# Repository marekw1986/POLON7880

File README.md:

# POLON 7880

## Overview

This is repository stores modified version of TinyBasic interpreter for 8080 based microcomputers. 
It has been customized to my homemade system, based on Polish clone of mentioned CPU - 
CEMI MCY7880. Original code has been supplemented with I/O routines supporting built-in 
peripherals.

Computer is described on my [Hackaday.io profile](https://hackaday.io/project/161333-polon-7880)

This project is still in development.

## Required tools

You need an [a86 cross assembler](https://github.com/glitchwrks/a85) to asemble this project.

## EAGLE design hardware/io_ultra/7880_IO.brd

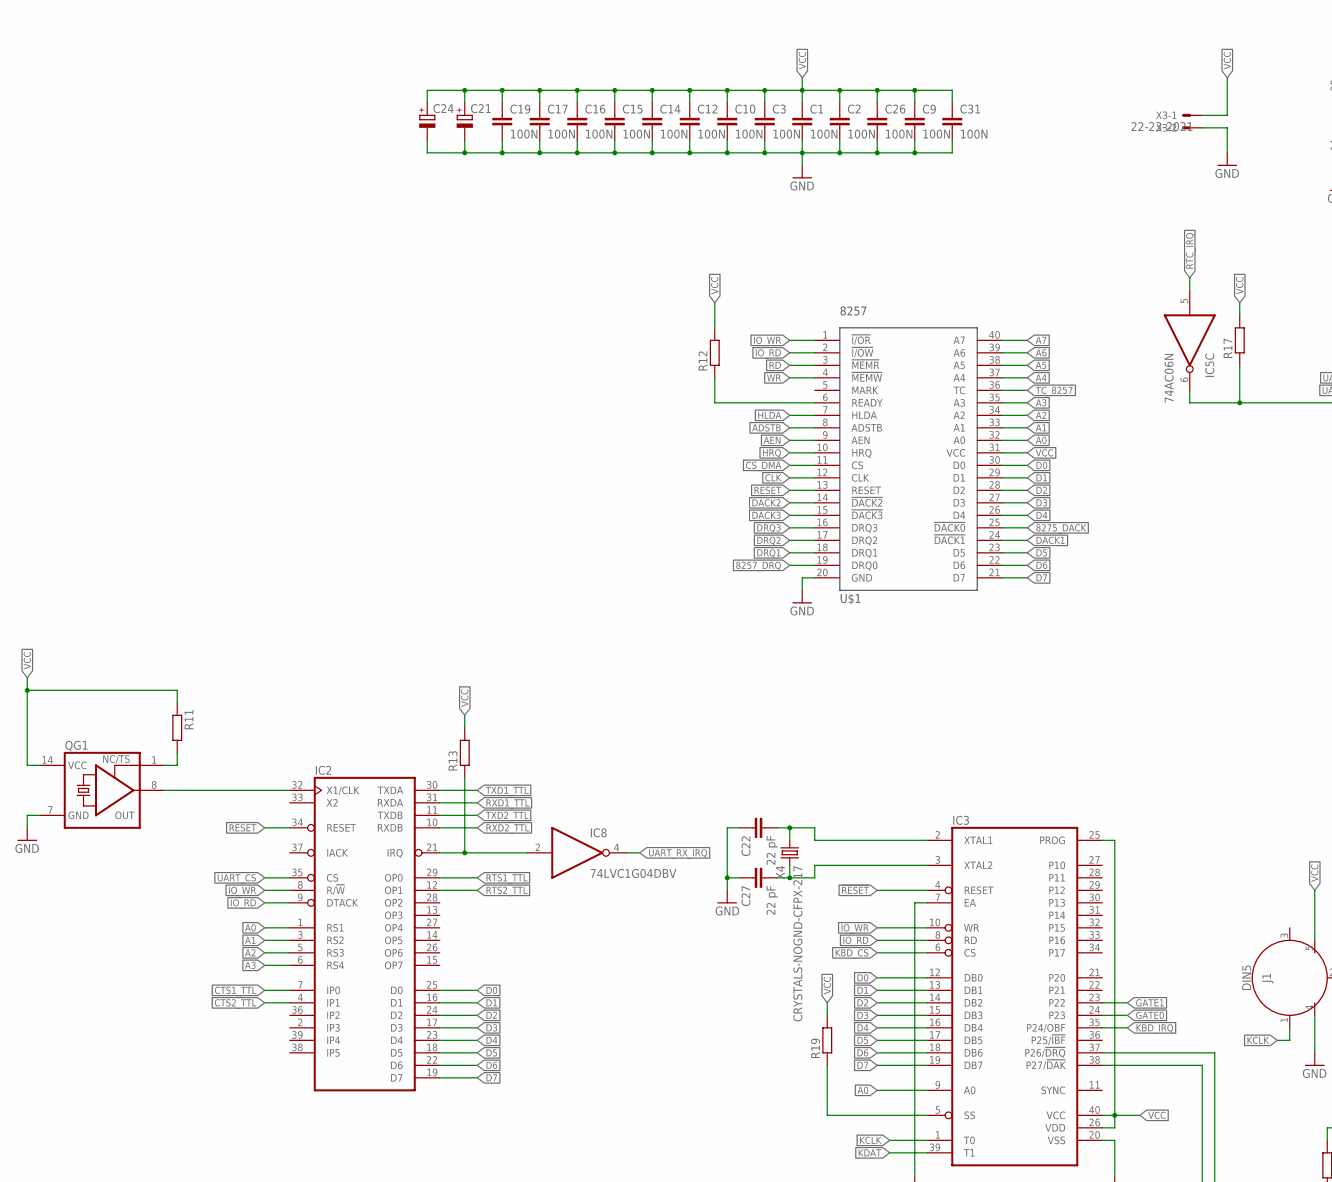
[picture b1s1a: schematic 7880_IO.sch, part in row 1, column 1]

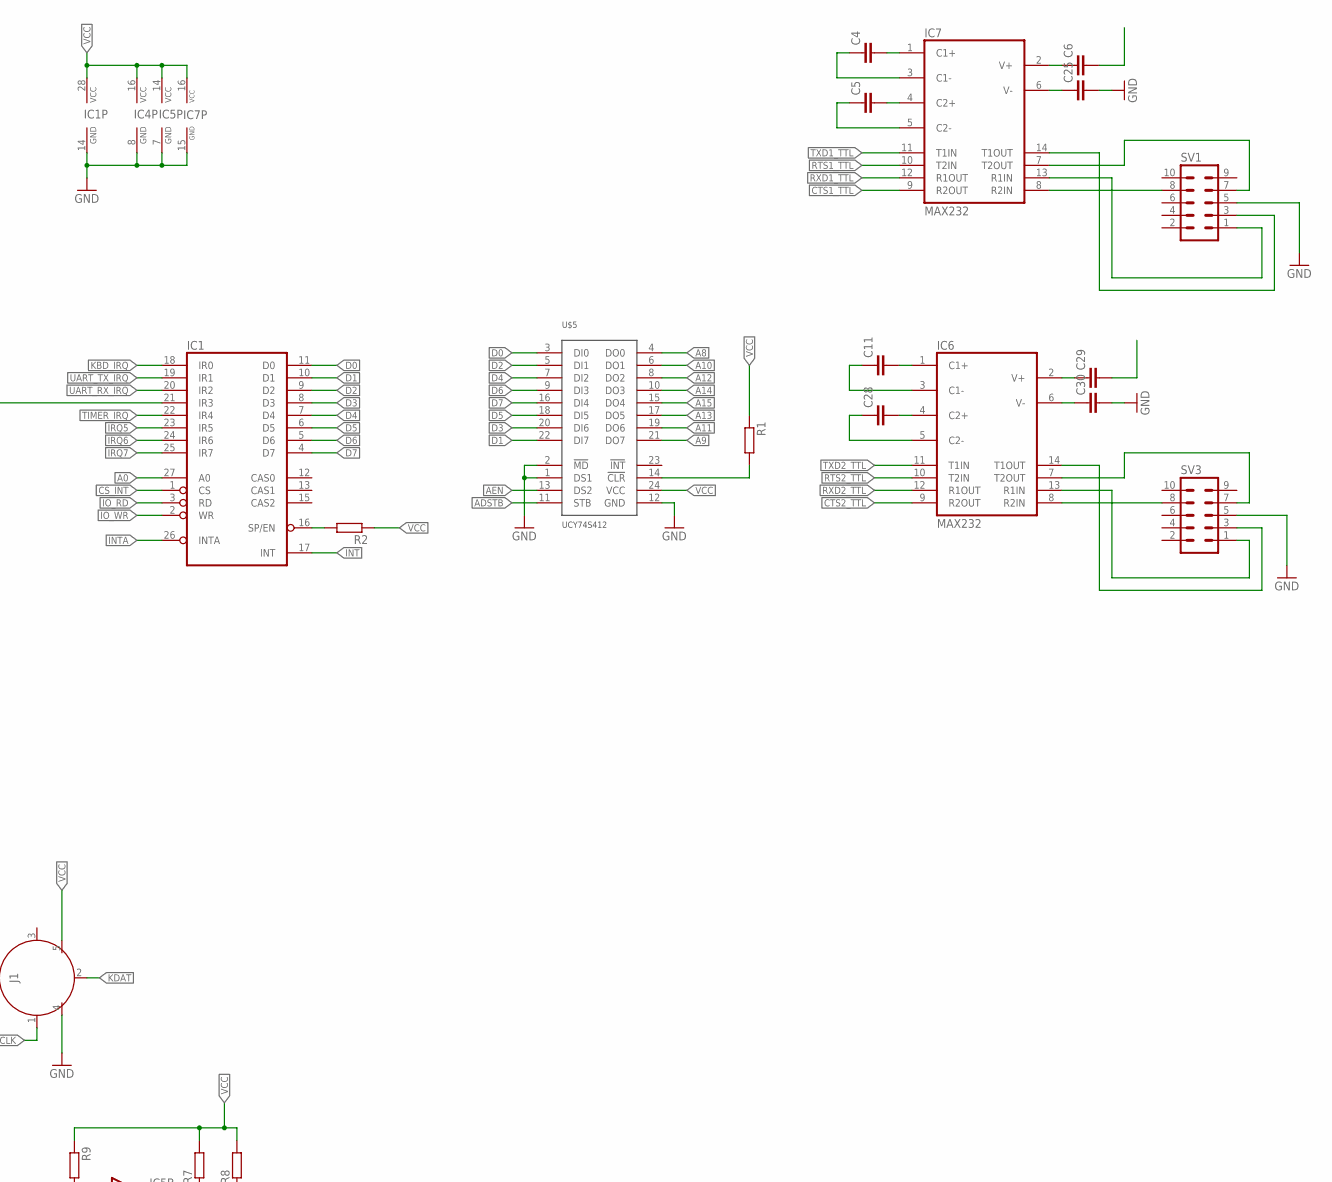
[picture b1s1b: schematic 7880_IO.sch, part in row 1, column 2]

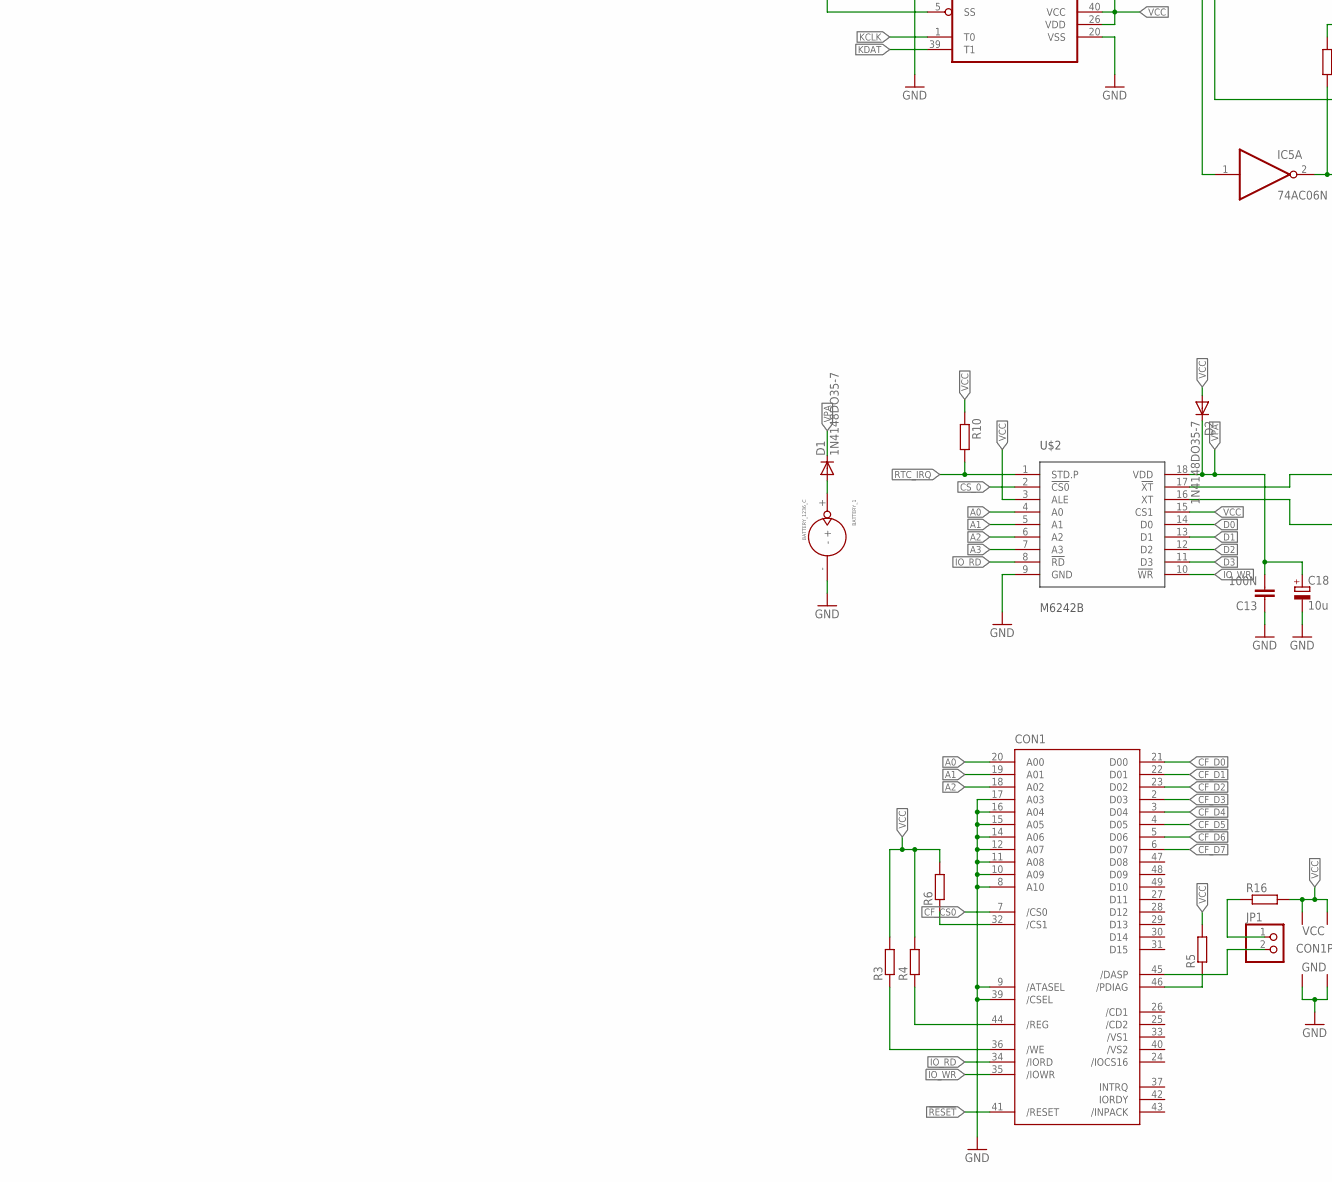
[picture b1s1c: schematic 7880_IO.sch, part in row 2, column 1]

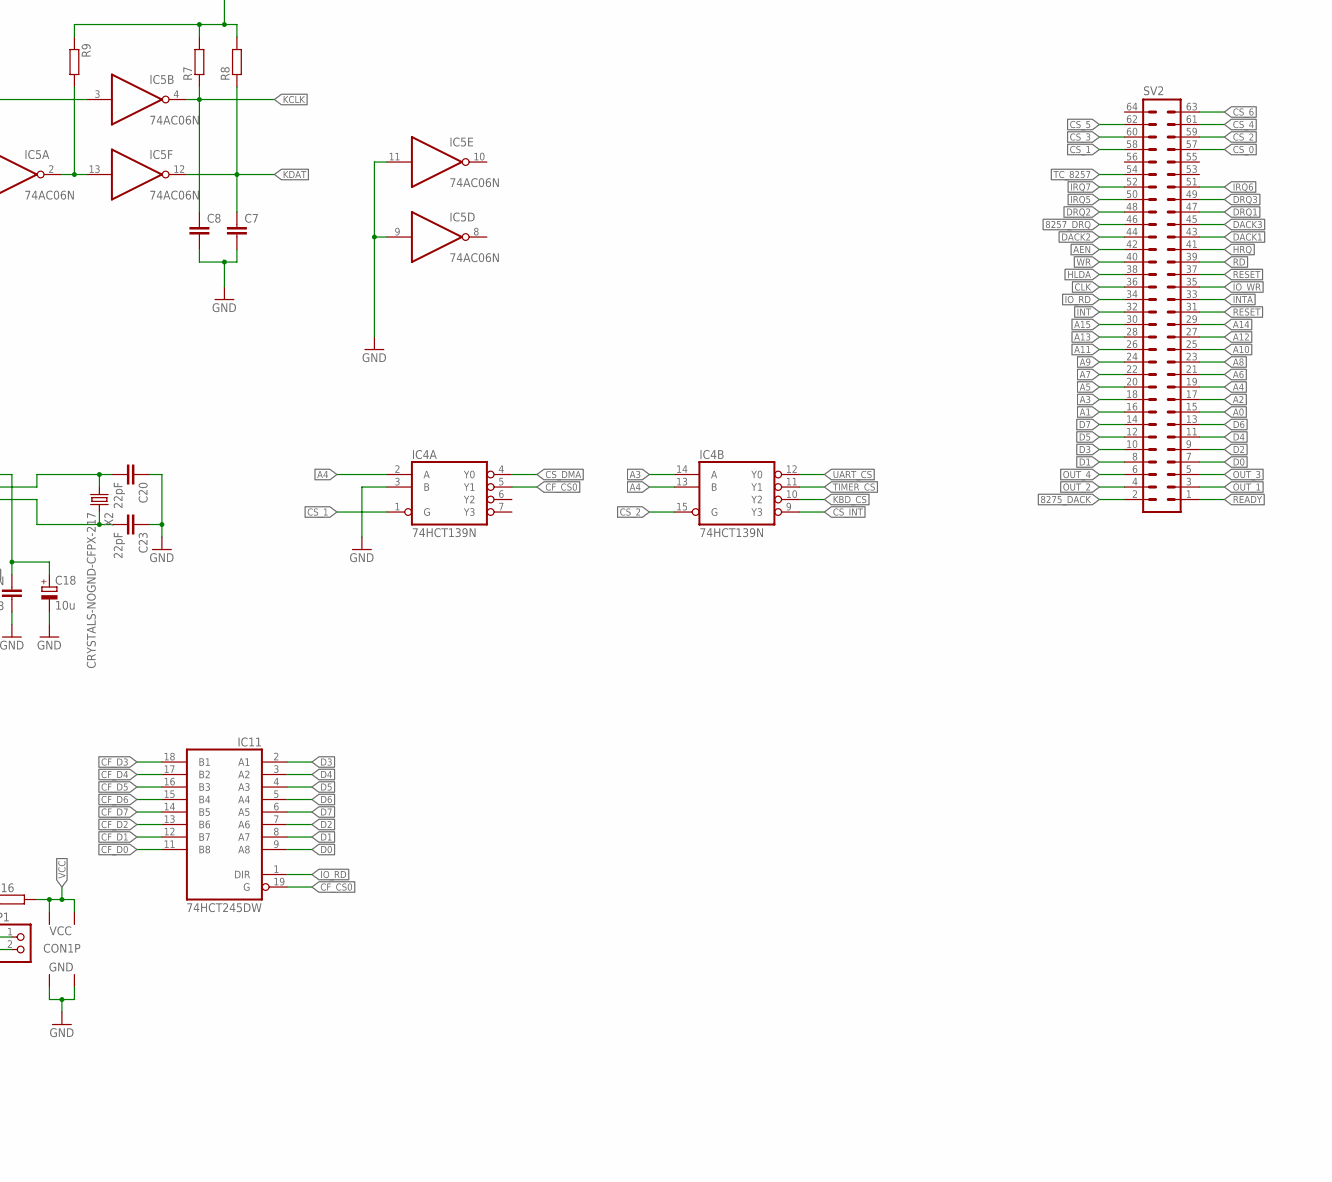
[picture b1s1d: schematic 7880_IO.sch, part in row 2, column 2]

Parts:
BATTERY_1: BATTERY_1236_C
C1, C2, C3, C9, C10, C12, C13, C14, C15, C16, C17, C19, C26, C31: 100N; C0603
C4, C5, C6, C7, C8, C11, C25, C28, C29, C30: C-EUC0603; C0603
C18: 10u; SMC_B
C20, C23: 22pF; C0603
C21: CPOL-EUE3.5-8; E3,5-8
C22, C27: 22 pF; C0603
C24: CPOL-EUSMCB; SMC_B
CON1: CF-CARD-IDE_MODE; MI20-50PD-SF
D1, D2: 1N4148DO35-7; DO35-7
IC1: 8259A; DIL28-6
IC2: MC68681P; DIL40
IC3: UPI-8042AH; DIL40
IC4: 74HCT139N; DIL16
IC5: 74AC06N; DIL14
IC6, IC7: MAX232; DIL16
IC8: 74LVC1G04DBV; SOT23-5
IC11: 74HCT245DW; SO20W
J1: DIN5; DIN5-RA-PTH
JP1: PINHD-1X2; 1X02
QG1: XO-14; DIL14S
R1, R2, R3, R6, R9, R10, R11, R12, R16: R-EU_R0603; R0603
R4, R13, R17: R-EU_0204/7; 0204/7
R5: R-EU_0207/10; 0207/10
R7, R19: R-EU_0204/5; 0204/5
R8: R-EU_M0805; M0805
SV1, SV3: ML10
SV2: ML64L
U$1: 8257; DIL40
U$2: M6242B; DIL18
U$5: UCY74S412; DIL24-6
X2, X4: CRYSTALS-NOGND-CFPX-217; 3.2X1.5-2-PAD
X3: 22-23-2021

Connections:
8257_DRQ: SV2.46, U$1.19 (DRQ0)
8275_DACK: SV2.2, U$1.25 (!DACK0)
2457600HZ: IC2.32 (X1/CLK), QG1.8 (OUT)
!RESET: CON1.41 (/RESET), IC3.4 (RESET), SV2.37
A0: CON1.20 (A00), IC1.27 (A0), IC2.1 (RS1), IC3.9 (A0), SV2.15, U$1.32 (A0), U$2.4 (A0)
A1: CON1.19 (A01), IC2.3 (RS2), SV2.16, U$1.33 (A1), U$2.5 (A1)
A2: CON1.18 (A02), IC2.5 (RS3), SV2.17, U$1.34 (A2), U$2.6 (A2)
A3: IC2.6 (RS4), IC4.14 (A), SV2.18, U$1.35 (A3), U$2.7 (A3)
A4: IC4.2 (A), IC4.13 (B), SV2.19, U$1.37 (A4)
A5: SV2.20, U$1.38 (A5)
A6: SV2.21, U$1.39 (A6)
A7: SV2.22, U$1.40 (A7)
A8: SV2.23, U$5.4 (DO0)
A9: SV2.24, U$5.21 (DO7)
A10: SV2.25, U$5.6 (DO1)
A11: SV2.26, U$5.19 (DO6)
A12: SV2.27, U$5.8 (DO2)
A13: SV2.28, U$5.17 (DO5)
A14: SV2.29, U$5.10 (DO3)
A15: SV2.30, U$5.15 (DO4)
ADSTB: U$1.8 (ADSTB), U$5.11 (STB)
AEN: SV2.42, U$1.9 (AEN), U$5.13 (DS2)
CF_CS0: CON1.7 (/CS0), IC4.5 (Y1), IC11.19 (G)
CF_D0: CON1.21 (D00), IC11.11 (B8)
CF_D1: CON1.22 (D01), IC11.12 (B7)
CF_D2: CON1.23 (D02), IC11.13 (B6)
CF_D3: CON1.2 (D03), IC11.18 (B1)
CF_D4: CON1.3 (D04), IC11.17 (B2)
CF_D5: CON1.4 (D05), IC11.16 (B3)
CF_D6: CON1.5 (D06), IC11.15 (B4)
CF_D7: CON1.6 (D07), IC11.14 (B5)
CLK: SV2.36, U$1.12 (CLK)
COM1_CTS: IC7.8 (R2IN), SV1.8
COM1_RXD: IC7.13 (R1IN), SV1.1
COM1_TXD: IC7.14 (T1OUT), SV1.3
CS_0: SV2.57, U$2.2 (!CS0)
CS_1: IC4.1 (G), SV2.58
CS_2: IC4.15 (G), SV2.59
CS_3: SV2.60
CS_4: SV2.61
CS_5: SV2.62
CS_6: SV2.63
CS_DMA: IC4.4 (Y0), U$1.11 (CS)
CS_INT: IC1.1 (CS), IC4.9 (Y3)
CTS1_TTL: IC2.7 (IP0), IC7.9 (R2OUT)
CTS2_TTL: IC2.4 (IP1), IC6.9 (R2OUT)
D0: IC1.11 (D0), IC2.25 (D0), IC3.12 (DB0), IC11.9 (A8), SV2.7, U$1.30 (D0), U$2.14 (D0), U$5.3 (DI0)
D1: IC1.10 (D1), IC2.16 (D1), IC3.13 (DB1), IC11.8 (A7), SV2.8, U$1.29 (D1), U$2.13 (D1), U$5.22 (DI7)
D2: IC1.9 (D2), IC2.24 (D2), IC3.14 (DB2), IC11.7 (A6), SV2.9, U$1.28 (D2), U$2.12 (D2), U$5.5 (DI1)
D3: IC1.8 (D3), IC2.17 (D3), IC3.15 (DB3), IC11.2 (A1), SV2.10, U$1.27 (D3), U$2.11 (D3), U$5.20 (DI6)
D4: IC1.7 (D4), IC2.23 (D4), IC3.16 (DB4), IC11.3 (A2), SV2.11, U$1.26 (D4), U$5.7 (DI2)
D5: IC1.6 (D5), IC2.18 (D5), IC3.17 (DB5), IC11.4 (A3), SV2.12, U$1.23 (D5), U$5.18 (DI5)
D6: IC1.5 (D6), IC2.22 (D6), IC3.18 (DB6), IC11.5 (A4), SV2.13, U$1.22 (D6), U$5.9 (DI3)
D7: IC1.4 (D7), IC2.19 (D7), IC3.19 (DB7), IC11.6 (A5), SV2.14, U$1.21 (D7), U$5.16 (DI4)
DACK1: SV2.43, U$1.24 (!DACK1)
DACK2: SV2.44, U$1.14 (!DACK2)
DACK3: SV2.45, U$1.15 (!DACK3)
DRQ1: SV2.47, U$1.18 (DRQ1)
DRQ2: SV2.48, U$1.17 (DRQ2)
DRQ3: SV2.49, U$1.16 (DRQ3)
GATE0: IC3.24 (P23)
GATE1: IC3.23 (P22)
GND: BATTERY_1.-, C1.2, C2.2, C3.2, C7.2, C8.2, C9.2, C10.2, C12.2, C13.1, C14.2, C15.2, C16.2, C17.2, C18.-, C19.2, C20.1, C21.-, C22.1, C23.1, C24.-, C25.2, C26.2, C27.1, C30.2, C31.2, CON1.1 (GND1), CON1.8 (A10), CON1.9 (/ATASEL), CON1.10 (A09), CON1.11 (A08), CON1.12 (A07), CON1.14 (A06), CON1.15 (A05), CON1.16 (A04), CON1.17 (A03), CON1.39 (/CSEL), CON1.50 (GND2), IC1.14 (GND), IC2.20 (GND), IC3.7 (EA), IC3.20 (VSS), IC4.3 (B), IC4.8 (GND), IC5.7 (GND), IC5.9 (I), IC5.11 (I), IC6.15 (GND), IC7.15 (GND), IC8.3 (GND), IC11.10 (GND), J1.4, QG1.7 (GND), SV1.5, SV3.5, U$1.20 (GND), U$2.9 (GND), U$5.1 (DS1), U$5.2 (!MD), U$5.12 (GND), X3.2
HLDA: SV2.38, U$1.7 (HLDA)
HRQ: SV2.41, U$1.10 (HRQ)
INT: IC1.17 (INT), SV2.32
INTA: IC1.26 (INTA), SV2.33
IO_RD: CON1.34 (/IORD), IC1.3 (RD), IC2.9 (DTACK), IC3.8 (RD), IC11.1 (DIR), SV2.34, U$1.2 (!I/OW), U$2.8 (!RD)
IO_WR: CON1.35 (/IOWR), IC1.2 (WR), IC2.8 (R/!W), IC3.10 (WR), SV2.35, U$1.1 (!I/OR), U$2.10 (!WR)
IRQ5: IC1.23 (IR5), SV2.50
IRQ6: IC1.24 (IR6), SV2.51
IRQ7: IC1.25 (IR7), SV2.52
KBD_CS: IC3.6 (CS), IC4.10 (Y2)
KBD_IRQ: IC1.18 (IR0), IC3.35 (P24/OBF)
KCLK: C8.1, IC3.1 (T0), IC5.4 (O), J1.1, R7.1
KDAT: C7.1, IC3.39 (T1), IC5.12 (O), J1.2, R8.1
unnamed: R1.2, U$5.14 (!CLR)
unnamed: IC1.16 (SP/EN), R2.2
unnamed: IC3.38 (P27/!DAK), IC5.1 (I)
unnamed: CON1.36 (/WE), R3.1
unnamed: R12.1, U$1.6 (READY)
unnamed: QG1.1 (TS), R11.2
unnamed: IC2.21 (IRQ), IC8.2 (I), R13.1
unnamed: C4.2, IC7.1 (C1+)
unnamed: C5.2, IC7.4 (C2+)
unnamed: C5.1, IC7.5 (C2-)
unnamed: C4.1, IC7.3 (C1-)
unnamed: C6.1, IC7.2 (V+)
unnamed: C25.1, IC7.6 (V-)
unnamed: IC6.7 (T2OUT), SV3.7
unnamed: C11.2, IC6.1 (C1+)
unnamed: IC3.37 (P26/!DRQ), IC5.3 (I)
unnamed: IC7.7 (T2OUT), SV1.7
unnamed: CON1.44 (/REG), R4.1
unnamed: IC5.2 (O), IC5.13 (I), R9.2
unnamed: CON1.46 (/PDIAG), R5.1
unnamed: BATTERY_1.+, D1.A
unnamed: C28.2, IC6.4 (C2+)
unnamed: C28.1, IC6.5 (C2-)
unnamed: CON1.32 (/CS1), R6.1
unnamed: C11.1, IC6.3 (C1-)
unnamed: C29.1, IC6.2 (V+)
unnamed: IC1.21 (IR3), IC5.6 (O), R17.1
unnamed: CON1.45 (/DASP), JP1.2
unnamed: JP1.1, R16.1
unnamed: IC3.5 (SS), R19.1
unnamed: IC6.13 (R1IN), SV3.1
unnamed: IC6.14 (T1OUT), SV3.3
unnamed: IC6.8 (R2IN), SV3.8
unnamed: C30.1, IC6.6 (V-)
OUT_1: SV2.3
OUT_2: SV2.4
OUT_3: SV2.5
OUT_4: SV2.6
RD: SV2.39, U$1.3 (!MEMR)
READY: SV2.1
RESET: IC2.34 (RESET), SV2.31, U$1.13 (RESET)
RTC_IRQ: IC5.5 (I), R10.2, U$2.1 (STD.P)
RTS1_TTL: IC2.29 (OP0), IC7.10 (T2IN)
RTS2_TTL: IC2.12 (OP1), IC6.10 (T2IN)
RXD1_TTL: IC2.31 (RXDA), IC7.12 (R1OUT)
RXD2_TTL: IC2.10 (RXDB), IC6.12 (R1OUT)
SOSCI: C20.2, U$2.17 (!XT), X2.1
SOSCO: C23.2, U$2.16 (XT), X2.2
TC_8257: SV2.54, U$1.36 (TC)
TIMER_CS: IC4.11 (Y1)
TIMER_IRQ: IC1.22 (IR4)
TXD1_TTL: IC2.30 (TXDA), IC7.11 (T1IN)
TXD2_TTL: IC2.11 (TXDB), IC6.11 (T1IN)
UART_CS: IC2.35 (CS), IC4.12 (Y0)
UART_RX_IRQ: IC1.20 (IR2), IC8.4 (O)
UART_TX_IRQ: IC1.19 (IR1)
VCC: C1.1, C2.1, C3.1, C6.2, C9.1, C10.1, C12.1, C14.1, C15.1, C16.1, C17.1, C19.1, C21.+, C24.+, C26.1, C29.2, C31.1, CON1.13 (VCC2), CON1.38 (VCC1), D2.A, IC1.28 (VCC), IC2.40 (VCC), IC3.25 (PROG), IC3.26 (VDD), IC3.40 (VCC), IC4.16 (VCC), IC5.14 (VCC), IC6.16 (VCC), IC7.16 (VCC), IC8.5 (VCC), IC11.20 (VCC), J1.5, QG1.14 (VCC), R1.1, R2.1, R3.2, R4.2, R5.2, R6.2, R7.2, R8.2, R9.1, R10.1, R11.1, R12.2, R13.2, R16.2, R17.2, R19.2, U$1.31 (VCC), U$2.3 (ALE), U$2.15 (CS1), U$5.24 (VCC), X3.1
VPA: C13.2, C18.+, D1.C, D2.C, U$2.18 (VDD)
WR: SV2.40, U$1.4 (!MEMW)
XTAL1: C22.2, IC3.2 (XTAL1), X4.1
XTAL2: C27.2, IC3.3 (XTAL2), X4.2

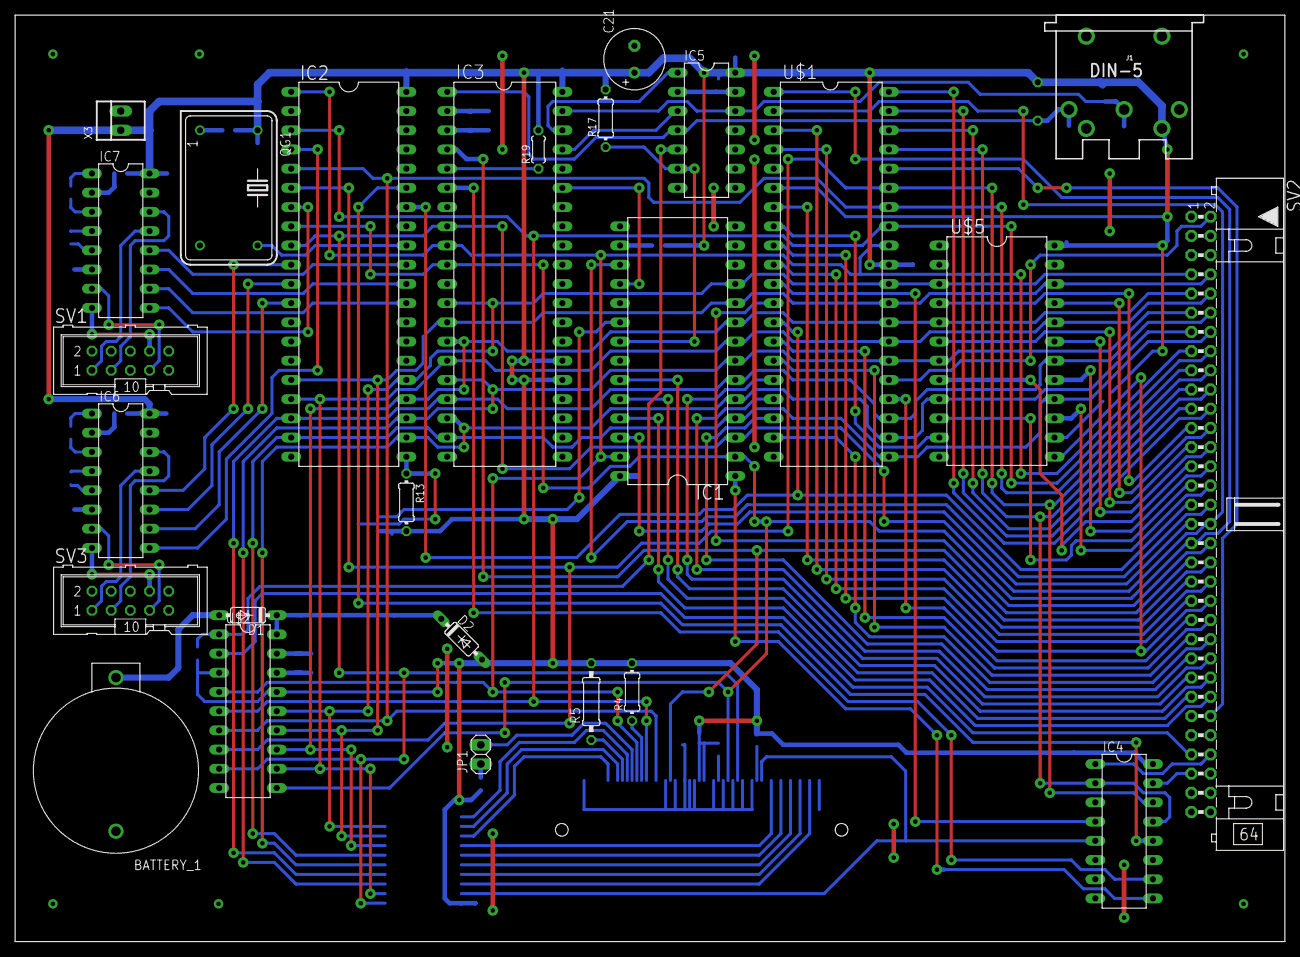
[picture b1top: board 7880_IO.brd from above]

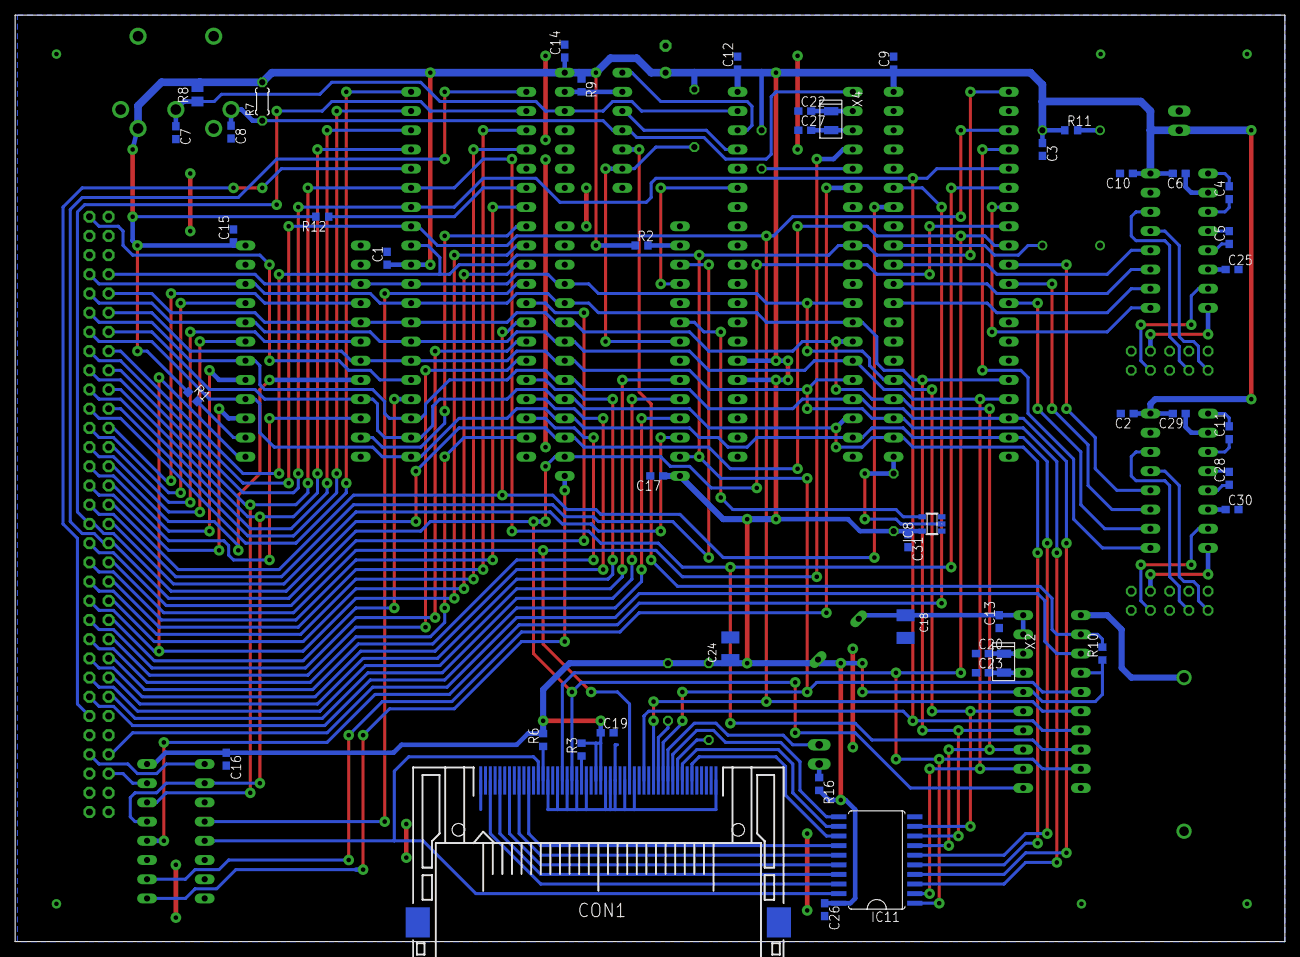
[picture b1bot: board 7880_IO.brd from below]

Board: 2 copper layers, 167.9 x 122.5 mm, 72 parts (46 on the bottom side), 123 nets.

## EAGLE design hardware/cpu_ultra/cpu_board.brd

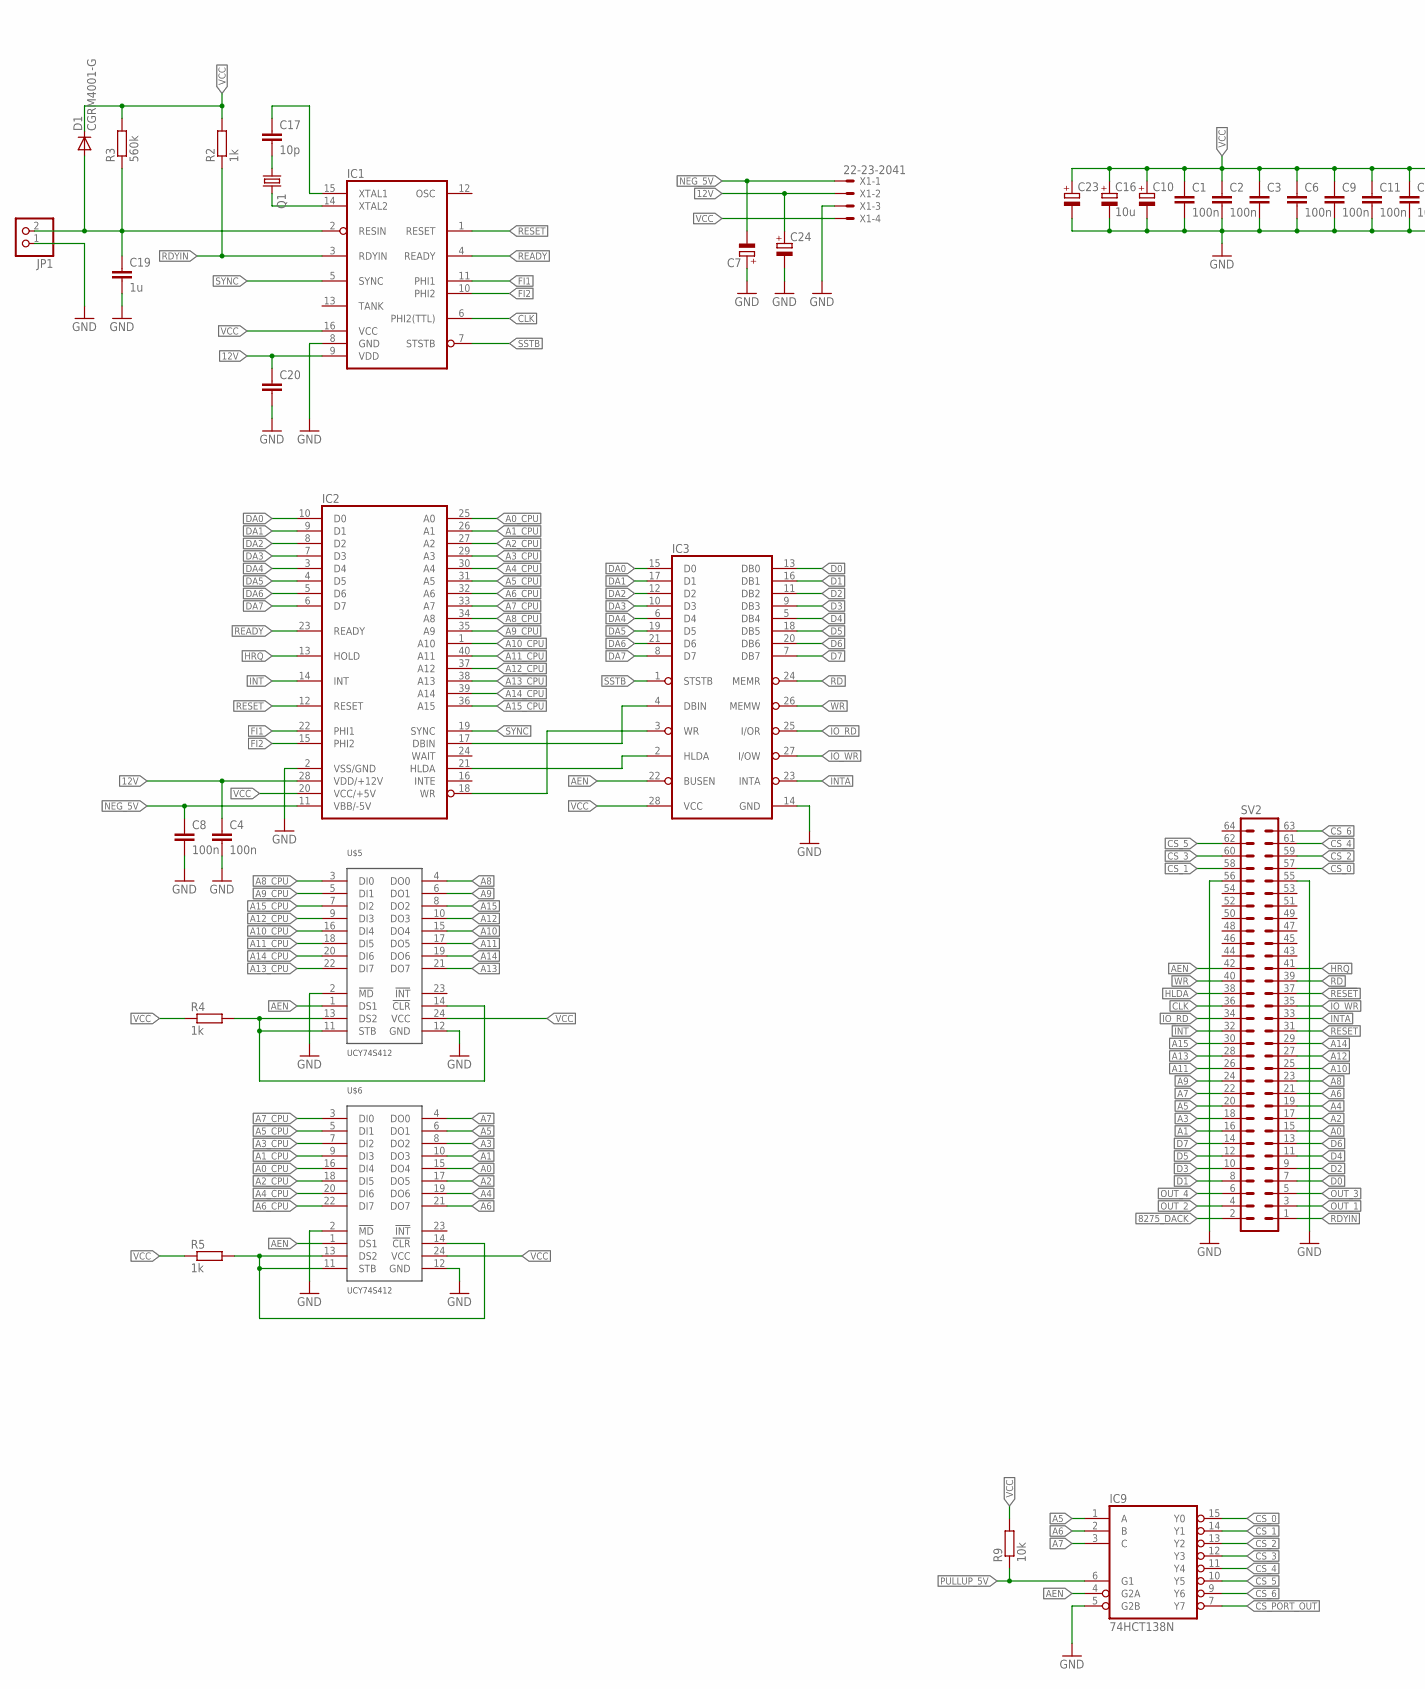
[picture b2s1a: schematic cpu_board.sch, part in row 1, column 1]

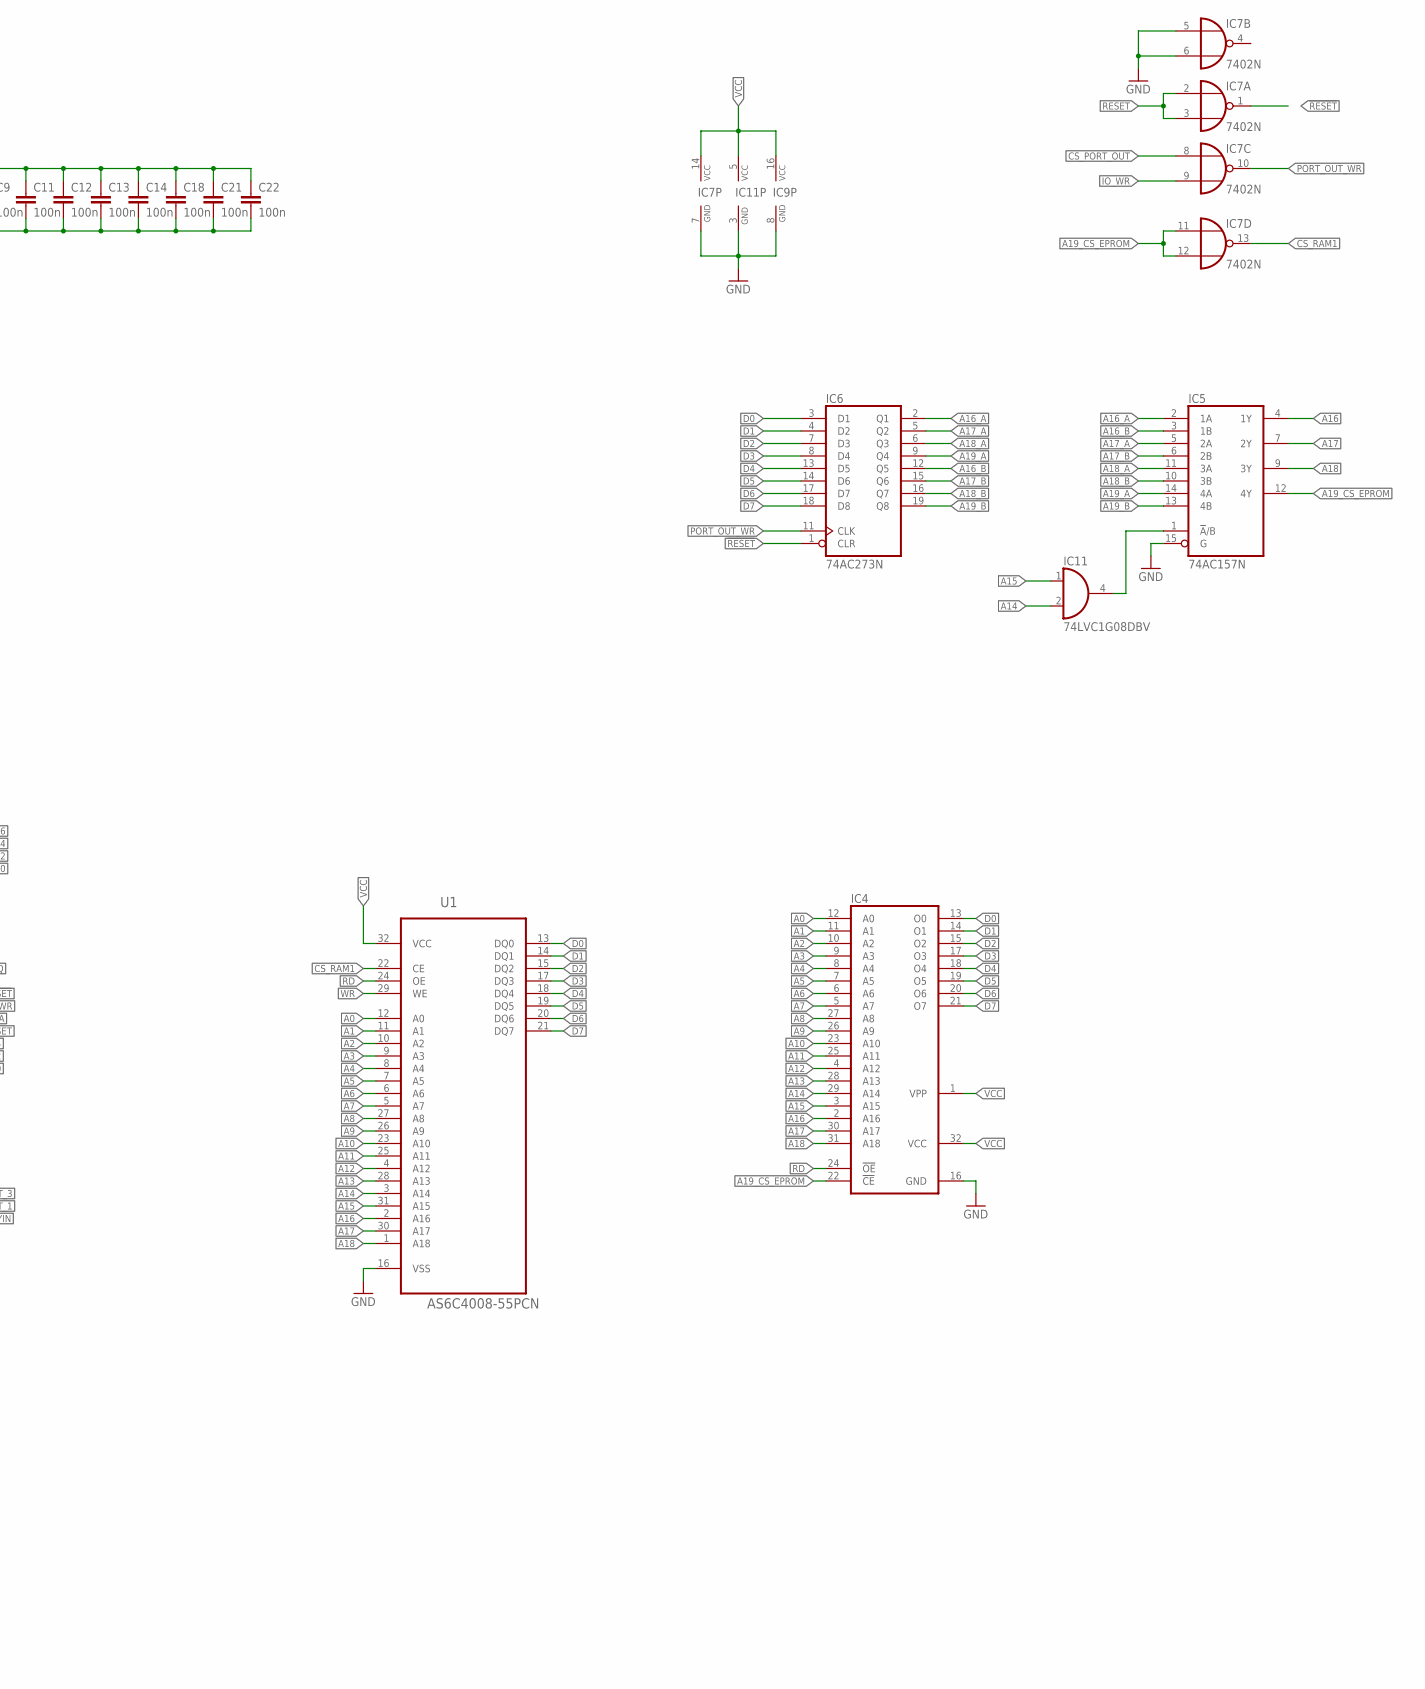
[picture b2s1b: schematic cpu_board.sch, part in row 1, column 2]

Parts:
C1, C2, C4, C6, C8, C21: 100n; C1206
C3, C20: C-EUC0603; C0603
C7: CPOL-EUE2.5-7; E2,5-7
C9, C14, C18, C22: 100n; C0603
C10, C23, C24: CPOL-EUE3.5-8; E3,5-8
C11, C12, C13: 100n; C0805
C16: 10u; SMC_B
C17: 10p; C0603
C19: 1u; C0603
D1: CGRM4001-G; SOD-123_MINI-SMA
IC1: 8224; DIL16
IC2: 8080; DIL40
IC3: 8228; DIL28-6
IC4: 27C4001D; DIL32
IC5: 74AC157N; DIL16
IC6: 74AC273N; DIL20
IC7: 7402N; DIL14
IC9: 74HCT138N; DIL16
IC11: 74LVC1G08DBV; SOT23-5
JP1: PINHD-1X2; 1X02
Q1: CRYSTALHC49U-V; HC49U-V
R2, R4: 1k; R0603
R3: 560k; R0603
R5: 1k; 0204/7
R9: 10k; R0603
SV2: ML64L
U1: AS6C4008-55PCN; DIP254P1524X393-32
U$5, U$6: UCY74S412; DIL24-6
X1: 22-23-2041

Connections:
12V: C4.1, C20.1, C24.+, IC1.9 (VDD), IC2.28 (VDD/+12V), X1.2
8275_DACK: SV2.2
!RESET: IC6.1 (CLR), IC7.1 (O), SV2.37
A0: IC4.12 (A0), SV2.15, U1.12 (A0), U$6.15 (DO4)
A0_CPU: IC2.25 (A0), U$6.16 (DI4)
A1: IC4.11 (A1), SV2.16, U1.11 (A1), U$6.10 (DO3)
A1_CPU: IC2.26 (A1), U$6.9 (DI3)
A2: IC4.10 (A2), SV2.17, U1.10 (A2), U$6.17 (DO5)
A2_CPU: IC2.27 (A2), U$6.18 (DI5)
A3: IC4.9 (A3), SV2.18, U1.9 (A3), U$6.8 (DO2)
A3_CPU: IC2.29 (A3), U$6.7 (DI2)
A4: IC4.8 (A4), SV2.19, U1.8 (A4), U$6.19 (DO6)
A4_CPU: IC2.30 (A4), U$6.20 (DI6)
A5: IC4.7 (A5), IC9.1 (A), SV2.20, U1.7 (A5), U$6.6 (DO1)
A5_CPU: IC2.31 (A5), U$6.5 (DI1)
A6: IC4.6 (A6), IC9.2 (B), SV2.21, U1.6 (A6), U$6.21 (DO7)
A6_CPU: IC2.32 (A6), U$6.22 (DI7)
A7: IC4.5 (A7), IC9.3 (C), SV2.22, U1.5 (A7), U$6.4 (DO0)
A7_CPU: IC2.33 (A7), U$6.3 (DI0)
A8: IC4.27 (A8), SV2.23, U1.27 (A8), U$5.4 (DO0)
A8_CPU: IC2.34 (A8), U$5.3 (DI0)
A9: IC4.26 (A9), SV2.24, U1.26 (A9), U$5.6 (DO1)
A9_CPU: IC2.35 (A9), U$5.5 (DI1)
A10: IC4.23 (A10), SV2.25, U1.23 (A10), U$5.15 (DO4)
A10_CPU: IC2.1 (A10), U$5.16 (DI4)
A11: IC4.25 (A11), SV2.26, U1.25 (A11), U$5.17 (DO5)
A11_CPU: IC2.40 (A11), U$5.18 (DI5)
A12: IC4.4 (A12), SV2.27, U1.4 (A12), U$5.10 (DO3)
A12_CPU: IC2.37 (A12), U$5.9 (DI3)
A13: IC4.28 (A13), SV2.28, U1.28 (A13), U$5.21 (DO7)
A13_CPU: IC2.38 (A13), U$5.22 (DI7)
A14: IC4.29 (A14), IC11.2 (I1), SV2.29, U1.3 (A14), U$5.19 (DO6)
A14_CPU: IC2.39 (A14), U$5.20 (DI6)
A15: IC4.3 (A15), IC11.1 (I0), SV2.30, U1.31 (A15), U$5.8 (DO2)
A15_CPU: IC2.36 (A15), U$5.7 (DI2)
A16: IC4.2 (A16), IC5.4 (1Y), U1.2 (A16)
A16_A: IC5.2 (1A), IC6.2 (Q1)
A16_B: IC5.3 (1B), IC6.12 (Q5)
A17: IC4.30 (A17), IC5.7 (2Y), U1.30 (A17)
A17_A: IC5.5 (2A), IC6.5 (Q2)
A17_B: IC5.6 (2B), IC6.15 (Q6)
A18: IC4.31 (A18), IC5.9 (3Y), U1.1 (A18)
A18_A: IC5.11 (3A), IC6.6 (Q3)
A18_B: IC5.10 (3B), IC6.16 (Q7)
A19_A: IC5.14 (4A), IC6.9 (Q4)
A19_B: IC5.13 (4B), IC6.19 (Q8)
A19_CS_EPROM: IC4.22 (!CE), IC5.12 (4Y), IC7.11 (I0), IC7.12 (I1)
AEN: IC3.22 (BUSEN), IC9.4 (G2A), SV2.42, U$5.1 (DS1), U$6.1 (DS1)
CLK: IC1.6 (PHI2(TTL)), SV2.36
CS_0: IC9.15 (Y0), SV2.57
CS_1: IC9.14 (Y1), SV2.58
CS_2: IC9.13 (Y2), SV2.59
CS_3: IC9.12 (Y3), SV2.60
CS_4: IC9.11 (Y4), SV2.61
CS_5: IC9.10 (Y5), SV2.62
CS_6: IC9.9 (Y6), SV2.63
CS_PORT_OUT: IC7.8 (I0), IC9.7 (Y7)
CS_RAM1: IC7.13 (O), U1.22 (CE)
D0: IC3.13 (DB0), IC4.13 (O0), IC6.3 (D1), SV2.7, U1.13 (DQ0)
D1: IC3.16 (DB1), IC4.14 (O1), IC6.4 (D2), SV2.8, U1.14 (DQ1)
D2: IC3.11 (DB2), IC4.15 (O2), IC6.7 (D3), SV2.9, U1.15 (DQ2)
D3: IC3.9 (DB3), IC4.17 (O3), IC6.8 (D4), SV2.10, U1.17 (DQ3)
D4: IC3.5 (DB4), IC4.18 (O4), IC6.13 (D5), SV2.11, U1.18 (DQ4)
D5: IC3.18 (DB5), IC4.19 (O5), IC6.14 (D6), SV2.12, U1.19 (DQ5)
D6: IC3.20 (DB6), IC4.20 (O6), IC6.17 (D7), SV2.13, U1.20 (DQ6)
D7: IC3.7 (DB7), IC4.21 (O7), IC6.18 (D8), SV2.14, U1.21 (DQ7)
DA0: IC2.10 (D0), IC3.15 (D0)
DA1: IC2.9 (D1), IC3.17 (D1)
DA2: IC2.8 (D2), IC3.12 (D2)
DA3: IC2.7 (D3), IC3.10 (D3)
DA4: IC2.3 (D4), IC3.6 (D4)
DA5: IC2.4 (D5), IC3.19 (D5)
DA6: IC2.5 (D6), IC3.21 (D6)
DA7: IC2.6 (D7), IC3.8 (D7)
FI1: IC1.11 (PHI1), IC2.22 (PHI1)
FI2: IC1.10 (PHI2), IC2.15 (PHI2)
GND: C1.2, C2.2, C3.2, C4.2, C6.2, C7.+, C8.2, C9.2, C10.-, C11.2, C12.2, C13.2, C14.2, C16.-, C18.2, C19.2, C20.2, C21.2, C22.2, C23.-, C24.-, IC1.8 (GND), IC2.2 (VSS/GND), IC3.14 (GND), IC4.16 (GND), IC5.8 (GND), IC5.15 (G), IC6.10 (GND), IC7.5 (I0), IC7.6 (I1), IC7.7 (GND), IC9.5 (G2B), IC9.8 (GND), IC11.3 (GND), JP1.1, SV2.55, SV2.56, U1.16 (VSS), U$5.2 (!MD), U$5.12 (GND), U$6.2 (!MD), U$6.12 (GND), X1.3
HLDA: IC2.21 (HLDA), IC3.2 (HLDA), SV2.38
HRQ: IC2.13 (HOLD), SV2.41
INT: IC2.14 (INT), SV2.32
INTA: IC3.23 (INTA), SV2.33
IO_RD: IC3.25 (I/OR), SV2.34
IO_WR: IC3.27 (I/OW), IC7.9 (I1), SV2.35
unnamed: IC2.17 (DBIN), IC3.4 (DBIN)
unnamed: IC5.1 (!A!/B), IC11.4 (O)
unnamed: IC2.18 (WR), IC3.3 (WR)
unnamed: IC1.14 (XTAL2), Q1.2
unnamed: C17.2, Q1.1
unnamed: C17.1, IC1.15 (XTAL1)
unnamed: C19.1, D1.A, IC1.2 (RESIN), JP1.2, R3.1
unnamed: R5.2, U$6.11 (STB), U$6.13 (DS2), U$6.14 (!CLR)
unnamed: R4.2, U$5.11 (STB), U$5.13 (DS2), U$5.14 (!CLR)
NEG_5V: C7.-, C8.1, IC2.11 (VBB/-5V), X1.1
OUT_1: SV2.3
OUT_2: SV2.4
OUT_3: SV2.5
OUT_4: SV2.6
PORT_OUT_WR: IC6.11 (CLK), IC7.10 (O)
PULLUP_5V: IC9.6 (G1), R9.1
RD: IC3.24 (MEMR), IC4.24 (!OE), SV2.39, U1.24 (OE)
RDYIN: IC1.3 (RDYIN), R2.1, SV2.1
READY: IC1.4 (READY), IC2.23 (READY)
RESET: IC1.1 (RESET), IC2.12 (RESET), IC7.2 (I0), IC7.3 (I1), SV2.31
SSTB: IC1.7 (STSTB), IC3.1 (STSTB)
SYNC: IC1.5 (SYNC), IC2.19 (SYNC)
VCC: C1.1, C2.1, C3.1, C6.1, C9.1, C10.+, C11.1, C12.1, C13.1, C14.1, C16.+, C18.1, C21.1, C22.1, C23.+, D1.C, IC1.16 (VCC), IC2.20 (VCC/+5V), IC3.28 (VCC), IC4.1 (VPP), IC4.32 (VCC), IC5.16 (VCC), IC6.20 (VCC), IC7.14 (VCC), IC9.16 (VCC), IC11.5 (VCC), R2.2, R3.2, R4.1, R5.1, R9.2, U1.32 (VCC), U$5.24 (VCC), U$6.24 (VCC), X1.4
WR: IC3.26 (MEMW), SV2.40, U1.29 (WE)

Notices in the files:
parts and their libraries:
SparkFun-Connectors: Licensing: Creative Commons ShareAlike 4.0 International - https://creativecommons.org/licenses/by-sa/4.0
